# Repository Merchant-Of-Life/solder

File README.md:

# Solder

A light-sensitive circuit using a photoresistor, an NPN transistor, and two LEDs. Powered by a 20mm coin cell battery.

## Schematic

## PCB

## RENDER

## Features

* Light-sensitive LED activation using a photoresistor
* Adjustable sensitivity via an onboard potentiometer
* Powered by a 20mm coin cell battery
* Easy to solder through-hole (THT) components

## BOM

* 1x 20mm Coin Cell Battery Holder (Keystone 3034 SMD)
* 2x 5mm LEDs
* 1x NPN Transistor (TO-92L)
* 1x Photoresistor (LDR 5.1x4.3mm)
* 1x 470Ω Resistor
* 1x Trim Potentiometer (Vishay T73YP)

Made by @Merchant-Of-Life on Slack :D

Falstad Simulation: https://www.falstad.com/s.php?s=7ohT6q

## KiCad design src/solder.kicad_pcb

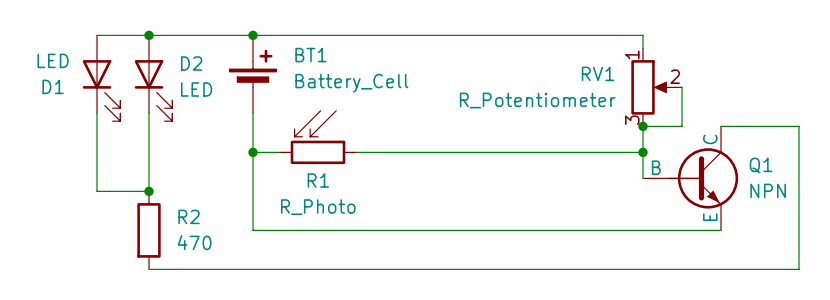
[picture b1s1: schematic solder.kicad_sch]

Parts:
BT1: Battery_Cell; BatteryHolder_Keystone_3034_1x20mm
D1, D2: LED; LED_D5.0mm
Q1: NPN; TO-92L_HandSolder
R1: R_Photo; R_LDR_5.1x4.3mm_P3.4mm_Vertical
R2: 470; R_Axial_DIN0207_L6.3mm_D2.5mm_P7.62mm_Horizontal
RV1: R_Potentiometer; Potentiometer_Vishay_T73YP_Vertical

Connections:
unnamed: BT1.1 (+), D1.2 (A), D2.2 (A), RV1.1
unnamed: BT1.2 (-), Q1.3 (E), R1.2
unnamed: D1.1 (K), D2.1 (K), R2.1
unnamed: Q1.2 (B), R1.1, RV1.2, RV1.3
unnamed: Q1.1 (C), R2.2

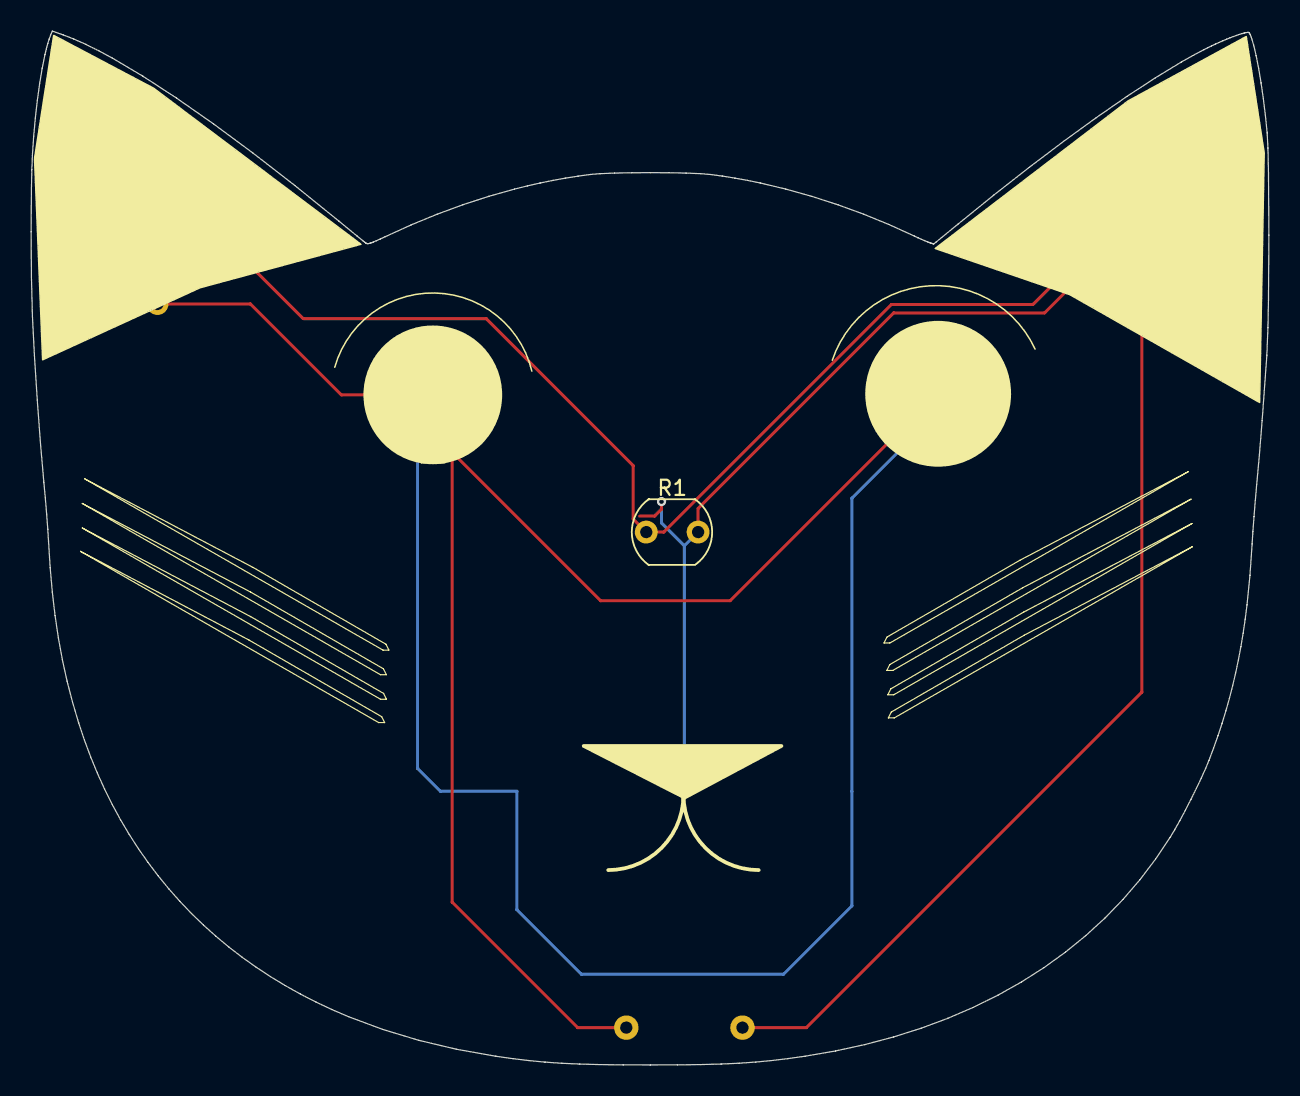
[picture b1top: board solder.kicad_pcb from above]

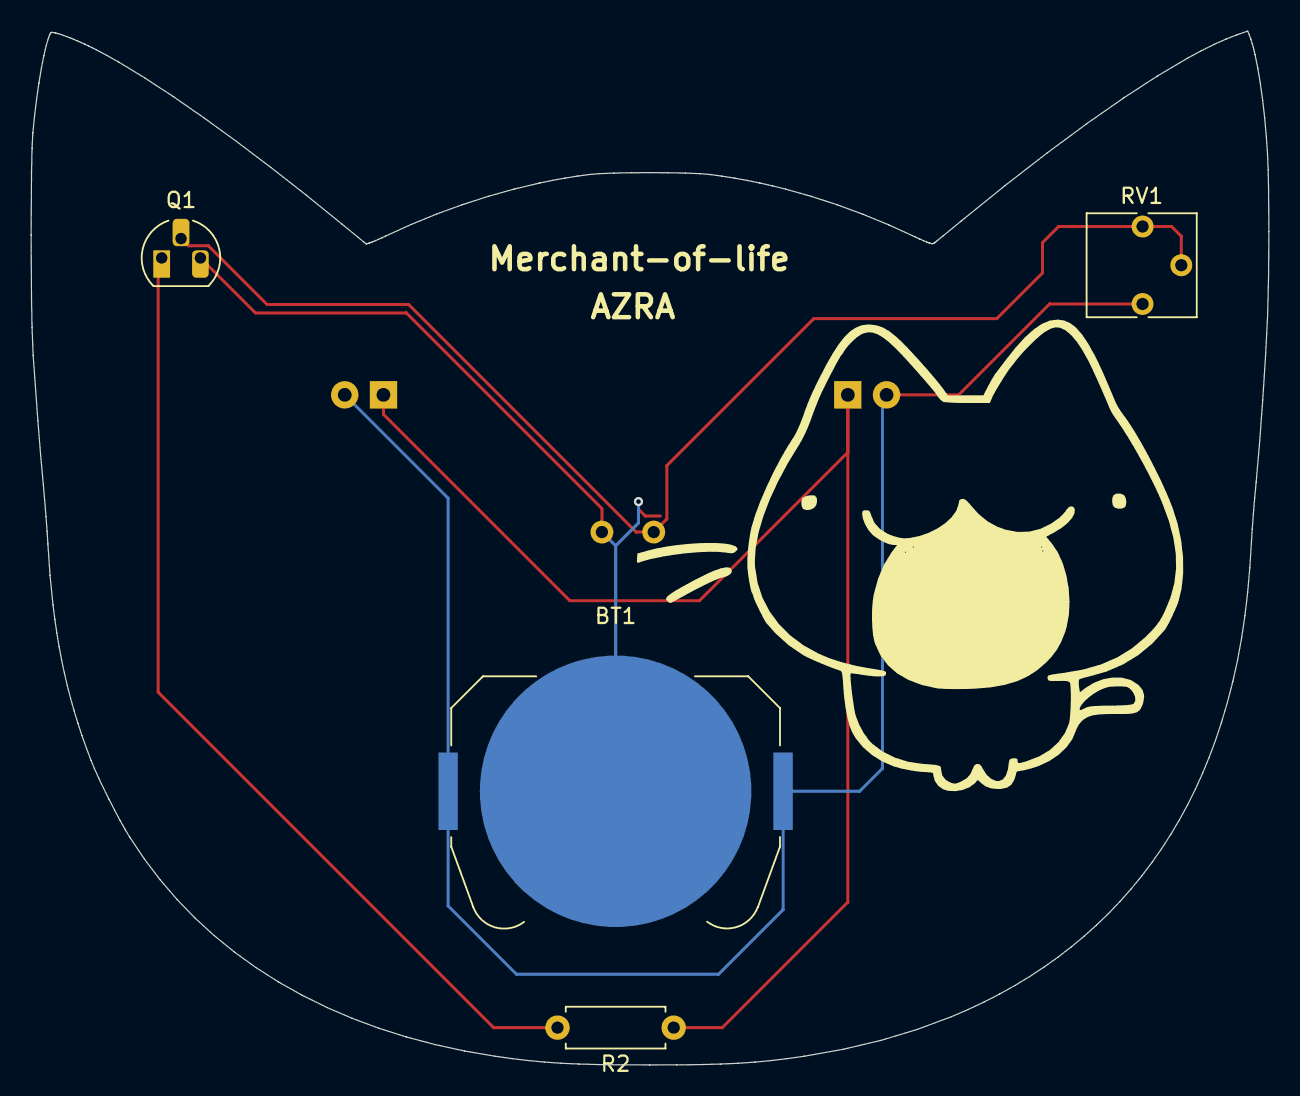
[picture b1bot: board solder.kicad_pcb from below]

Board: 2 copper layers, 81.2 x 67.8 mm, 7 parts (4 on the bottom side), 5 nets.
